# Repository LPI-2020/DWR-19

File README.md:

# Digital Waiter Robot (DWR -19)

Developed in:
- Projeto Integrador - LPI II (2021)

Members:
- Bruno Miguel Vasconcelos da Silva, a88289
- Diogo Miguel Cunha Fernandes, a88262
- Duarte Miguel Novo Rodrigues, a88259
- Francisco Lopes Salgado, a88231 
- João Pedro Dias Miranda, a88237
- José Tomás Lima de Abreu, a88218

Directed by:
- Luís André Magalhães de Barros

Short description (PT):
- A ideia do produto surgiu da necessidade de atuar perante o panorama pandémico (Covid-19), mais propriamente no auxílio a pessoas que se encontrem em isolamento.
- Uma pessoa em isolamento não pode ter contacto com o mundo exterior. Por este motivo, pensou-se em desenvolver um robô que faça chegar bens essenciais à pessoa em isolamento.
-	A função principal do produto será desempenhar o papel de um “empregado de mesa”, daí o nome “Waiter”. O termo “Digital” advém do facto de todas funcionalidades serem maioritariamente implementadas de forma digital, perfazendo o nome do robô “Digital Waiter Robot”.

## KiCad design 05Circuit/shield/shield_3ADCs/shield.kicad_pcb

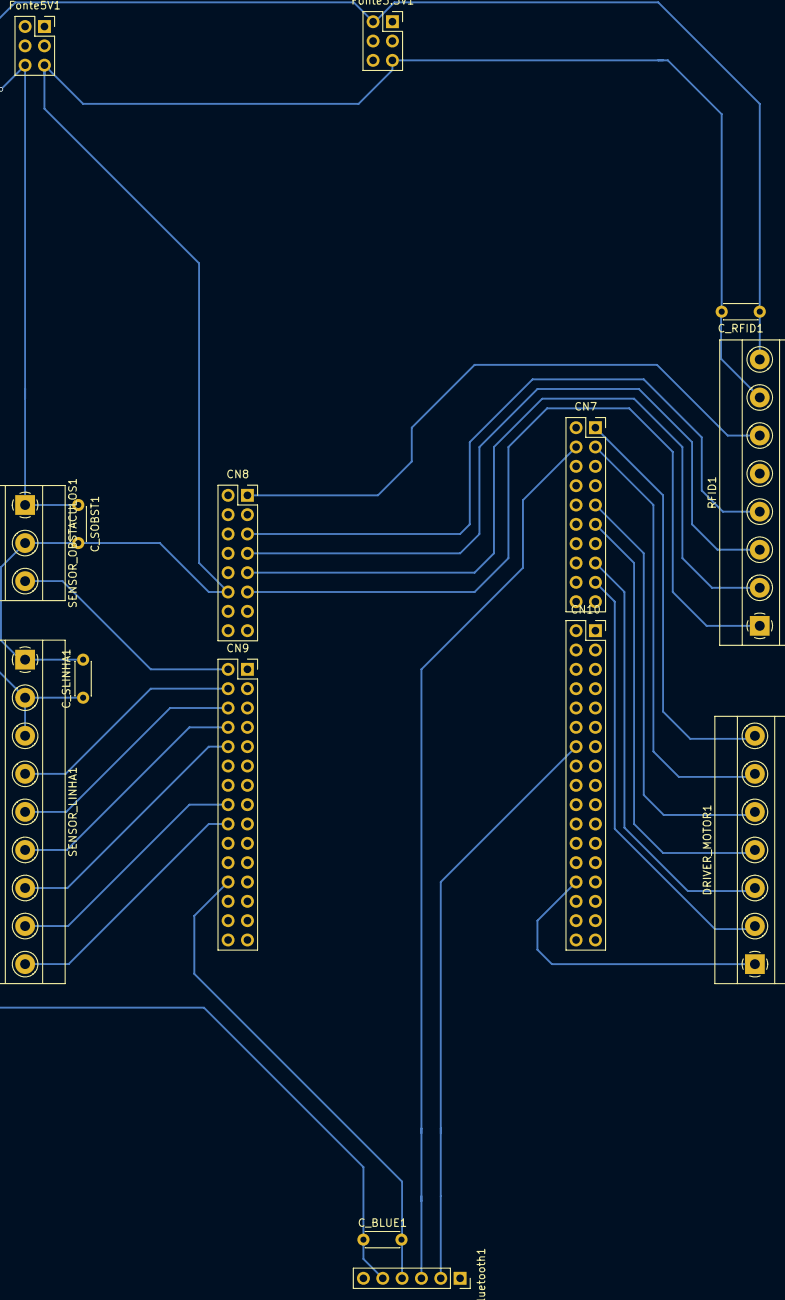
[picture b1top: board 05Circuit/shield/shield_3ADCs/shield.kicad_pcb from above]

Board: 2 copper layers, 15 parts (0 on the bottom side), 26 nets.

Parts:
CN7: Digital; PinSocket_2x10_P2.54mm_Vertical
CN8: Digital; PinSocket_2x08_P2.54mm_Vertical
CN9: Digital; PinSocket_2x15_P2.54mm_Vertical
CN10: Digital; PinSocket_2x17_P2.54mm_Vertical
C_BLUE1: C; C_Disc_D4.3mm_W1.9mm_P5.00mm
C_RFID1: C; C_Disc_D4.3mm_W1.9mm_P5.00mm
C_SLINHA1: C; C_Disc_D4.3mm_W1.9mm_P5.00mm
C_SOBST1: C; C_Disc_D4.3mm_W1.9mm_P5.00mm
DRIVER_MOTOR1: Screw_Terminal_01x07; TerminalBlock_Phoenix_MKDS-1,5-7_1x07_P5.00mm_Horizontal
Fonte3.3V1, Fonte5V1: Digital; PinSocket_2x03_P2.54mm_Vertical
RFID1: Screw_Terminal_01x06; TerminalBlock_Phoenix_MKDS-1,5-8_1x08_P5.00mm_Horizontal
SENSOR_LINHA1: Screw_Terminal_01x09; TerminalBlock_Phoenix_MKDS-1,5-9_1x09_P5.00mm_Horizontal
SENSOR_OBSTACULOS1: Screw_Terminal_01x03; TerminalBlock_Phoenix_MKDS-1,5-3_1x03_P5.00mm_Horizontal
bluetooth1: Digital; PinSocket_1x06_P2.54mm_Vertical

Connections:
+3.3V: C_RFID1.1, C_SLINHA1.1, Fonte3.3V1.2, Fonte3.3V1.6, RFID1.8, SENSOR_LINHA1.2, SENSOR_LINHA1.3
+5V: C_BLUE1.1, C_SOBST1.1, Fonte5V1.2, Fonte5V1.6, SENSOR_OBSTACULOS1.1, bluetooth1.5
/AVDD: CN7.5, CN10.2
/NC: CN8.2, CN9.14
/PA3: CN9.2, SENSOR_OBSTACULOS1.3
/PA5: CN7.9, DRIVER_MOTOR1.5
/PA6: CN7.11, DRIVER_MOTOR1.4
/PA7: CN7.13, CN9.16, SENSOR_LINHA1.8
/PB6: CN10.14, bluetooth1.2
/PB8: CN7.1, DRIVER_MOTOR1.7
/PB9: CN7.3, DRIVER_MOTOR1.6
/PB15: CN7.4, bluetooth1.3
/PC0: CN9.4, SENSOR_LINHA1.4
/PC3: CN9.6, SENSOR_LINHA1.5
/PC8: CN8.1, RFID1.6
/PC10: CN8.5, RFID1.4
/PC11: CN8.7, RFID1.3
/PC12: CN8.9, RFID1.2
/PD2: CN8.11, RFID1.1
/PD14: CN7.15, DRIVER_MOTOR1.3
/PD15: CN7.17, DRIVER_MOTOR1.2
/PE2: CN9.13, CN10.26
/PF2: CN9.18, SENSOR_LINHA1.9
/PF3: CN9.8, SENSOR_LINHA1.6
/PF5: CN9.10, SENSOR_LINHA1.7
GND: CN7.7, CN8.12, CN8.14, CN9.11, CN9.24, CN10.6, CN10.18, CN10.21, CN10.28, C_BLUE1.2, C_RFID1.2, C_SLINHA1.2, C_SOBST1.2, DRIVER_MOTOR1.1, Fonte3.3V1.1, Fonte3.3V1.5, Fonte5V1.1, Fonte5V1.5, RFID1.7, SENSOR_LINHA1.1, SENSOR_OBSTACULOS1.2, bluetooth1.4

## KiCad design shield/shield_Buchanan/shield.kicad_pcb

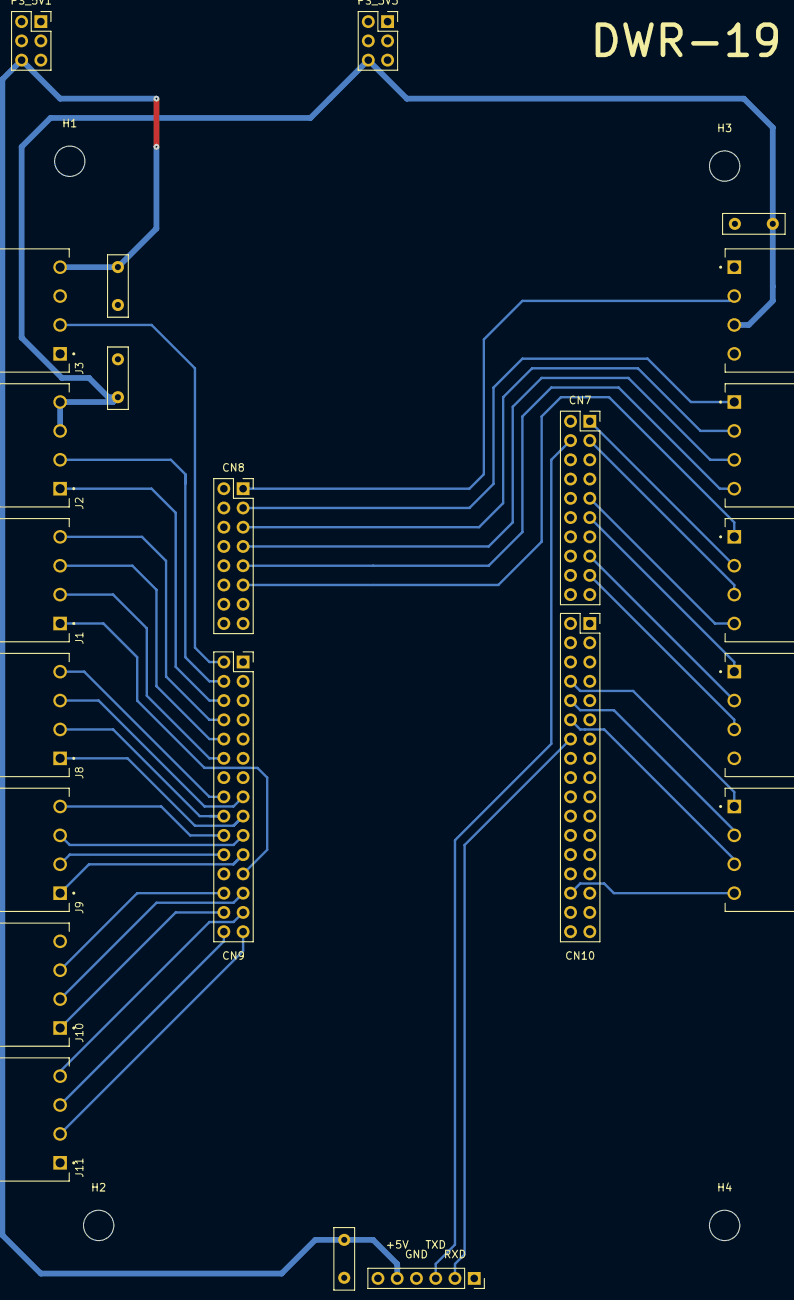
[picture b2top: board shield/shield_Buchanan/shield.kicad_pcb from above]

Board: 2 copper layers, 27 parts (0 on the bottom side), 45 nets.

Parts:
Bluetooth1: Conn_01x06; PinSocket_1x06_P2.54mm_Vertical
CN7: Conn_02x10_Odd_Even; PinSocket_2x10_P2.54mm_Vertical
CN8: Conn_02x08_Odd_Even; PinSocket_2x08_P2.54mm_Vertical
CN9: Conn_02x15_Odd_Even; PinSocket_2x15_P2.54mm_Vertical
CN10: Conn_02x17_Odd_Even; PinSocket_2x17_P2.54mm_Vertical
C_BLUE1: C; C_Disc_D8.0mm_W2.5mm_P5.00mm
C_RFID1: C; C_Disc_D8.0mm_W2.5mm_P5.00mm
C_SLINHA1: C; C_Disc_D8.0mm_W2.5mm_P5.00mm
C_SOBST1: C; C_Disc_D8.0mm_W2.5mm_P5.00mm
H1, H2, H3, H4: MountingHole; MountingHole_4mm
J1, J2, J3, J4, J5, J6, J7, J8, J9, J10, J11, J12: Screw_Terminal_01x04; TE_284513-4
PS_3V3, PS_5V1: Screw_Terminal_02x03; PinSocket_2x03_P2.54mm_Vertical

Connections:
+3V3: C_RFID1.1, C_SLINHA1.1, J2.3, J2.4, J7.3, PS_3V3.2, PS_3V3.6
+5V: Bluetooth1.5, C_BLUE1.1, C_SOBST1.1, J3.4, PS_5V1.2, PS_5V1.6
AVDD: CN7.5, CN10.2
GND: Bluetooth1.4, CN7.7, CN8.12, CN8.14, CN9.11, CN9.24, CN10.6, CN10.18, CN10.21, CN10.28, C_BLUE1.2, C_RFID1.2, C_SLINHA1.2, C_SOBST1.2, J3.1, J3.3, J4.4, J7.1, J7.4, J10.4, PS_3V3.1, PS_3V3.5, PS_5V1.1, PS_5V1.5
NC: CN8.2, CN9.14
PA0: CN10.30, J12.4
PA3: CN9.2, J3.2
PA5: CN7.9, J5.4
PA6: CN7.11, J4.1
PA7: CN7.13, CN9.16, J8.4
PB1: CN10.8, J12.1
PB6: Bluetooth1.2, CN10.14
PB8: CN7.1, J5.2
PB9: CN7.3, J5.3
PB15: Bluetooth1.3, CN7.4
PC0: CN9.4, J2.2
PC2: CN10.10, J12.2
PC3: CN9.6, J2.1
PC8: CN8.1, J7.2
PC9: CN8.3, J6.1
PC10: CN8.5, J6.2
PC11: CN8.7, J6.3
PC12: CN8.9, J6.4
PD0: CN9.26, J10.3
PD1: CN9.28, J10.1
PD2: CN8.11, J5.1
PD14: CN7.15, J4.2
PD15: CN7.17, J4.3
PE2: CN9.13, CN10.26
PE3: CN9.21, J9.1
PE4: CN9.15, J8.3
PE5: CN9.17, J8.1
PE6: CN9.19, J9.3
PF0: CN9.22, J9.2
PF1: CN9.20, J9.4
PF2: CN9.18, J8.2
PF3: CN9.8, J1.4
PF4: CN10.12, J12.3
PF5: CN9.10, J1.3
PF7: CN9.25, J10.2
PF8: CN9.23, J1.1
PF9: CN9.27, J11.4
PF10: CN9.12, J1.2
PG0: CN9.30, J11.3
PG1: CN9.29, J11.2

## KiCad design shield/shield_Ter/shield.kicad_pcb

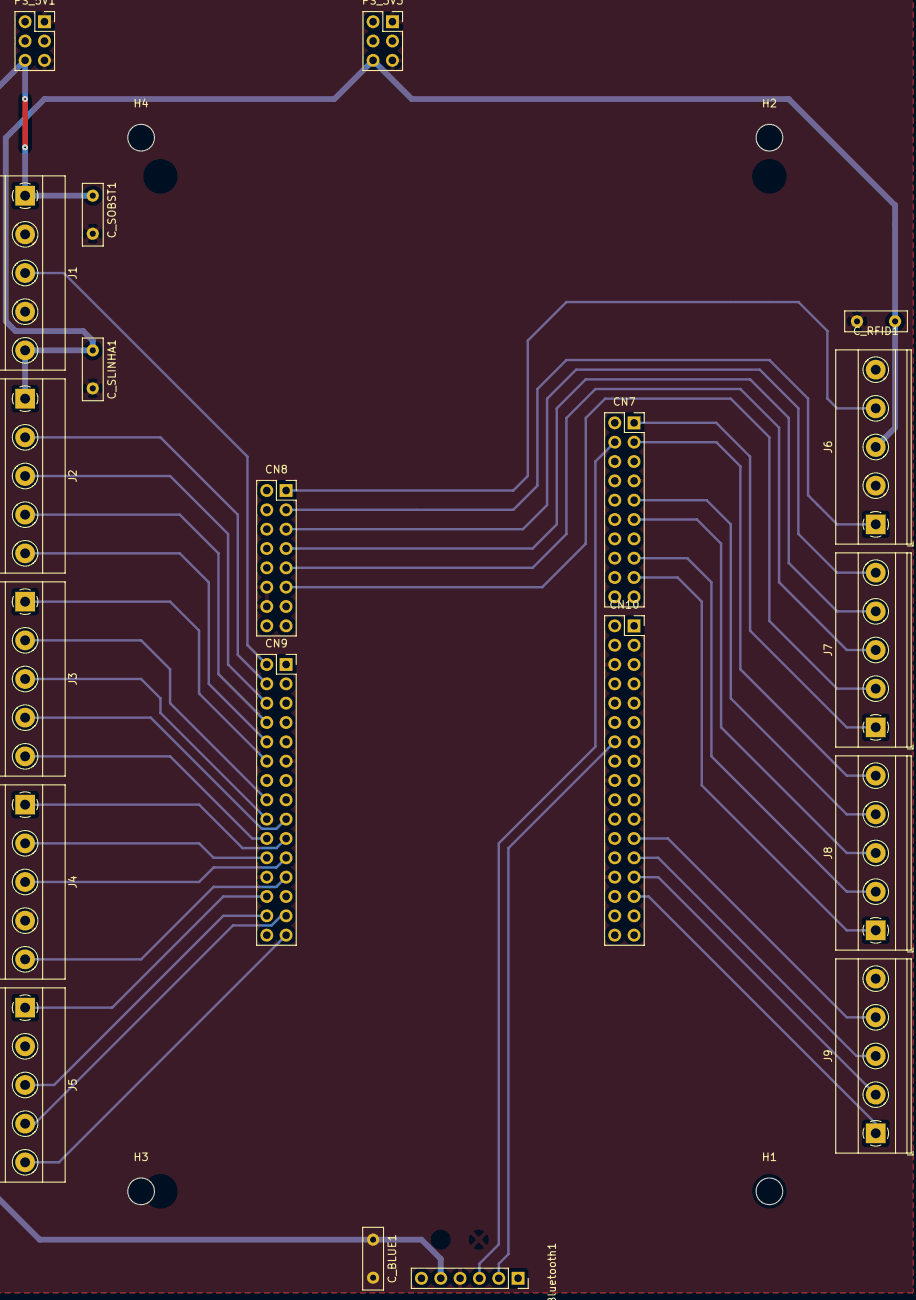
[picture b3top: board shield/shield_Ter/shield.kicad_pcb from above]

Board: 2 copper layers, 24 parts (0 on the bottom side), 42 nets.

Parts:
Bluetooth1: Conn_01x06; PinSocket_1x06_P2.54mm_Vertical
CN7: Conn_02x10_Odd_Even; PinSocket_2x10_P2.54mm_Vertical
CN8: Conn_02x08_Odd_Even; PinSocket_2x08_P2.54mm_Vertical
CN9: Conn_02x15_Odd_Even; PinSocket_2x15_P2.54mm_Vertical
CN10: Conn_02x17_Odd_Even; PinSocket_2x17_P2.54mm_Vertical
C_BLUE1: C; C_Disc_D8.0mm_W2.5mm_P5.00mm
C_RFID1: C; C_Disc_D8.0mm_W2.5mm_P5.00mm
C_SLINHA1: C; C_Disc_D8.0mm_W2.5mm_P5.00mm
C_SOBST1: C; C_Disc_D8.0mm_W2.5mm_P5.00mm
H1, H2, H3, H4: MountingHole; MountingHole_3.5mm
J1, J2, J3, J4, J5: Screw_Terminal_01x05; TerminalBlock_Phoenix_MKDS-1,5-5-5.08_1x05_P5.08mm_Horizont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
J6, J7, J8, J9: Screw_Terminal_01x04; TerminalBlock_Phoenix_MKDS-1,5-5-5.08_1x05_P5.08mm_Horizont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
PS_3V3, PS_5V1: Screw_Terminal_02x03; PinSocket_2x03_P2.54mm_Vertical

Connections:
+3V3: C_RFID1.1, C_SLINHA1.1, J1.5, J2.1, J6.3, PS_3V3.2, PS_3V3.6
+5V: Bluetooth1.5, C_BLUE1.1, C_SOBST1.1, J1.1, PS_5V1.2, PS_5V1.6
AVDD: CN7.5, CN10.2
GND: Bluetooth1.4, CN7.7, CN8.12, CN8.14, CN9.11, CN9.24, CN10.6, CN10.18, CN10.21, CN10.28, C_BLUE1.2, C_RFID1.2, C_SLINHA1.2, C_SOBST1.2, J1.2, J1.4, J4.4, J6.2, J6.5, J9.5, PS_3V3.1, PS_3V3.5, PS_5V1.1, PS_5V1.5
NC: CN8.2, CN9.14
PA3: CN9.2, J1.3
PA5: CN7.9, J8.4
PA6: CN7.11, J8.3
PA7: CN7.13, CN9.16, J3.2
PB6: Bluetooth1.2, CN10.14
PB8: CN7.1, J7.1
PB9: CN7.3, J8.5
PB15: Bluetooth1.3, CN7.4
PC0: CN9.4, J2.2
PC3: CN9.6, J2.3
PC8: CN8.1, J6.4
PC9: CN8.3, J6.1
PC10: CN8.5, J7.5
PC11: CN8.7, J7.4
PC12: CN8.9, J7.3
PD0: CN9.26, J5.1
PD1: CN9.28, J5.3
PD2: CN8.11, J7.2
PD14: CN7.15, J8.2
PD15: CN7.17, J8.1
PE2: CN9.13, CN10.26
PE3: CN9.21, J4.3
PE5: CN9.17, J3.4
PE6: CN9.19, J4.1
PE10: CN10.23, J9.4
PE12: CN10.25, J9.3
PE14: CN10.27, J9.2
PE15: CN10.29, J9.1
PF0: CN9.22, J4.2
PF1: CN9.20, J3.5
PF2: CN9.18, J3.3
PF3: CN9.8, J2.4
PF5: CN9.10, J2.5
PF8: CN9.23, J4.5
PF9: CN9.27, J5.4
PF10: CN9.12, J3.1
PG1: CN9.29, J5.5

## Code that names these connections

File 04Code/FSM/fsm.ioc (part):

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Mcu.UserName=STM32F767ZITx
PC10.Signal=SPI3_SCK
PC12.Signal=SPI3_MOSI
PB14.GPIO_Label=DEBUG_LRED
PC0.GPIOParameters=GPIO_Label
PC0.GPIO_Label=SENSOR1
PA3.GPIOParameters=GPIO_Label
PB0.GPIO_Label=DEBUG_LGREEN
PA6.GPIO_Label=IN1_LEFT
PB6.GPIO_Label=BLUET_TX
PD2.GPIOParameters=GPIO_Label
PB15.Signal=USART1_RX
PD9.Mode=Asynchronous
RCC.SYSCLKSource=RCC_SYSCLKSOURCE_PLLCLK
PD15.GPIOParameters=GPIO_Label
PB6.Signal=USART1_TX
PB6.Mode=Asynchronous
PC3.Signal=ADCx_IN13
PD8.Signal=USART3_TX
PF10.GPIO_Label=SENSOR6
RCC.HSE_VALUE=25000000
PB0.GPIOParameters=GPIO_Label
PB1.GPIO_Label=BUZZER
PB7.Signal=GPIO_Output
PF8.Mode=IN6
PF3.Signal=ADC3_IN9
PB6.GPIOParameters=GPIO_Label
PB7.GPIO_Label=DEBUG_LBLUE
PC8.GPIOParameters=GPIO_PuPd,GPIO_Label
Mcu.Package=LQFP144
PB9.Signal=GPIO_Output
PB1.Signal=GPIO_Output
PA6.Signal=GPIO_Output
PF8.GPIOParameters=GPIO_Label
PF5.GPIO_Label=SENSOR5
PF8.Signal=ADC3_IN6
PA5.GPIOParameters=GPIO_Label
PC11.Mode=Full_Duplex_Master
PB14.GPIOParameters=GPIO_Label
PF5.Signal=ADC3_IN15
PF10.Mode=IN8
PF3.GPIO_Label=SENSOR4
PD15.Signal=S_TIM4_CH4
PA3.Signal=ADCx_IN3
PA6.GPIOParameters=GPIO_Label
PD15.GPIO_Label=PWM_LEFT
PB8.GPIOParameters=GPIO_Label
PF3.Mode=IN9
PB9.GPIO_Label=IN1_RIGHT
PC11.Signal=SPI3_MISO
PC8.Signal=GPIO_Input
PC10.Mode=Full_Duplex_Master
PD9.Signal=USART3_RX
PC0.Signal=ADCx_IN10
PF5.Mode=IN15
PF8.GPIO_Label=SENSOR8
PB9.GPIOParameters=GPIO_Label
PC3.GPIOParameters=GPIO_Label
PC8.GPIO_Label=USER_BTN
PB8.GPIO_Label=PWM_RIGHT
PB7.GPIOParameters=GPIO_Label
PF5.GPIOParameters=GPIO_Label
PD8.Mode=Asynchronous
PF3.GPIOParameters=GPIO_Label
PB14.Signal=GPIO_Output
PA5.Signal=GPIO_Output
PC12.Mode=Full_Duplex_Master
board=custom
PB15.Mode=Asynchronous
PB15.GPIO_Label=BLUET_RX
PF10.Signal=ADC3_IN8
PD14.GPIO_Label=IN2_LEFT
PB15.GPIOParameters=GPIO_Label
Mcu.Name=STM32F767ZITx
PD14.Signal=GPIO_Output
PC8.GPIO_PuPd=GPIO_PULLDOWN
PD14.GPIOParameters=GPIO_Label
RCC.SYSCLKFreq_VALUE=216000000
PA5.GPIO_Label=IN2_RIGHT
PF10.GPIOParameters=GPIO_Label
PB8.Signal=S_TIM4_CH3
PC3.GPIO_Label=SENSOR3
PD2.Signal=GPIO_Output
PB0.Signal=GPIO_Output
PD2.GPIO_Label=SPI3_SDA
PA3.GPIO_Label=OBS_DETECTOR
PB1.GPIOParameters=GPIO_Label

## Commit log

2021-02-26 add etapa 0
2021-02-26 To use in the future
2021-03-08 Etapa1-v1
2021-03-08 Added working time table
2021-03-08 Logbook
2021-03-10 planeamento acabado
2021-03-11 Added components
2021-03-15 Starting Etapa1
2021-03-17 Etapa1
2021-03-18 fast update
2021-03-18 Etapa1 done
2021-03-25 Minor corrections
2021-03-25 table index
2021-03-25 etapa 1 done v2
2021-03-25 Etapa1 pdf
2021-03-25 References fix
2021-03-29 Logbook update
2021-03-31 read sensor values with DMA
2021-03-31 Added stop mark sensor Flowchart
2021-03-31 Added obstacles sensor flowchart
2021-04-01 Added System diagrams
2021-04-01 Sensors readme update
2021-04-01 Module readme update
2021-04-01 Joao/Duarte update logbook -> day 31/03
2021-04-14 Added RFID code, Updated logbook and components list
2021-04-14 Updated RFID Readme files
2021-05-03 System diagram update
2021-05-04 Logbook yesterday
2021-05-04 pdf Titles changed
2021-05-05 Added documentation
2021-05-05 Detectors debug
2021-05-05 add seguidor de linha
2021-05-05 update RFID module
2021-06-01 Working on Stop Sensors
2021-06-01 linefollower code
2021-06-02 qtr dma
2021-06-03 Controlador PID feito (valores Kp,Ki,Kd escolhidos) | diagrama PID
2021-06-03 Stop sensors done
2021-06-03 turn
2021-06-04 Added battery schema
2021-06-04 Added Bluetooth
2021-06-04 rotate clean code
2021-06-05 Adding comments
2021-06-05 little changes on PID algorithm
2021-06-06 update log book
2021-06-07 Line follower
2021-06-07 Working on PID
2021-06-07 Speed extra
2021-06-07 Get speed macro
2021-06-07 RFID - SPI3 (needs testing)
    Code for RFID to work with SPI3.
    - Changed SP1 to SPI3: PINS A6, A7, A8 changed to C10, C11 and P12
2021-06-07 Updated Logbook and added Perifericos
2021-06-07 Testing move module
2021-06-07 Bluetooth - Added USART 1 functionality
2021-06-08 some corrections line top speed. Not working anyway
2021-06-08 Revert "Updated Logbook and added Perifericos"
    This reverts commit dbdd964fc060a66478d0325b46005da320524534.
2021-06-08 Updated Bluetooth, Added Cmd parsing
2021-06-08 pin excel v1
2021-06-08 perifericos updat
    e
2021-06-08 Merging FSM configs
2021-06-08 edit pinout excel, add pinout kicad
2021-06-09 line sensor 6 adc
2021-06-09 Testing stop sensors
2021-06-09 errors detected: lacks 'lf_rotate' from lineFollower
2021-06-09 shield 7 ADCs e perifericos
2021-06-09 added debounce
2021-06-09 Working on lfollower
2021-06-09 Cleaned RFID.c (only SPI3 folder)
    Won't modify SPI1 RFID to in order to keep a backup
2021-06-09 Added Comments
2021-06-09 Added Diagramas
2021-06-09 merging files to FSM
2021-06-10 Changed pins and peripherals in use FSM
2021-06-10 pcb conetores demasiado caros
2021-06-10 word
2021-06-10 PCB with Aquario con
2021-06-10 Corrected PCB
2021-06-10 PCB ready with buchanan conectors
2021-06-10 Obstacle detector
2021-06-10 QTR version
2021-06-10 texto maquina de estados
2021-06-10 Perifericos
2021-06-10 Diogo Updates
2021-06-10 Update PCB with new pins -> ADC3
2021-06-10 pcb adc 3
2021-06-10 PID text uptade
2021-06-10 read_RFID function and struct | test rfid in tests.c
2021-06-10 Update PID and State Machine text
2021-06-10 Test stop sensors
2021-06-11 rfid checks
2021-06-11 FSM testing
2021-06-11 Updated Diagrams
2021-06-11 Corrected RFID SPI3
2021-06-11 Test peripherals
2021-06-11 last update Kicad
2021-06-11 word pid
2021-06-12 add PID_ISR
2021-06-12 Update Bluetooth
2021-06-12 pid word update
2021-06-12 motion module
2021-06-12 motion
2021-06-12 receives one time and dont receives more chars
2021-06-12 PID followchart upadate. Word update
2021-06-12 Review word FSMPID
2021-06-12 rm ~docx
2021-06-12 Removing commented code
2021-06-12 qtr get digital/analog values
2021-06-12 Timeout module
2021-06-12 Rellocated timers. Timeout timer max 140sec
2021-06-12 Timeout update
2021-06-13 writing tests
2021-06-13 logbook components
2021-06-13 Error module
2021-06-13 Buracos 4mm
2021-06-13 motion testing
2021-06-13 timeout period
2021-06-13 Ficheiros Gerber!
2021-06-13 Testing Cross Detector
2021-06-13 testing rfid
2021-06-14 Added deobunce
2021-06-14 Capitulo Alimentacao e Mecanico
2021-06-14 Add ordem trabalhos
2021-06-14 testing
2021-06-14 receiving in fsm
2021-06-14 atulizaçao do logbook | lista de componentes | ordem de trabalhos
2021-06-14 fotos dos materiais
2021-06-14 fsm bluet using
2021-06-14 DMA (pouca coisa)
2021-06-14 dia pouco produtivo
2021-06-14 merging
2021-06-14 pid completed - no review done
2021-06-15 PID Word update (Offset explained)-> no review
2021-06-15 DMA acabado
2021-06-15 stop condition in motion isr
2021-06-15 Testing debounce
2021-06-15 circuitos de alimentacao update
2021-06-15 Diagrams Updated
2021-06-15 circuito mecanico - 1 review
2021-06-15 lineflw ok
2021-06-15 testing fsm
2021-06-15 correcao PID adc diagrama
2021-06-15 DMA -> EN
2021-06-15 Tsting Fsm
2021-06-16 relatorio - timers
2021-06-16 Uart added and small fixes to spi
2021-06-16 Updated Diagrams (~98% done)
2021-06-16 next move
2021-06-16 Diagrams 99% done - pdf preview available
    Still needs front sensor
2021-06-16 comentarios e possiveis correcoes SPI
2021-06-16 rfid
2021-06-16 UART possiveis correcoes
2021-06-16 atualização do SPI | inicio da tabela de perifericos
2021-06-16 mudança da pasta da shield
2021-06-16 Completed Mechanical Diagrams
2021-06-16 Fixing timeouts
2021-06-17 introducao
2021-06-17 update relatorio RFID e Bluetooth
2021-06-17 Added Bluetooth drawio diagram (not completed)
2021-06-17 Topicos Relatorio
2021-06-17 Tabelas de perifericos
2021-06-17 atualizaçao dos capitulos
2021-06-17 corpo do relatorio
2021-06-17 rfid number: cross duarte's bedroom
2021-06-17 fsm returning
2021-06-17 FSM finished
2021-06-18 Added sensores
2021-06-18 sys_diagram_v2
2021-06-18 Bluetooth Diagram
2021-06-18 DMA e ADC corrigido e adicionado ao relatorio
2021-06-18 Arquitetura e Modulos Utilizados in progress
2021-06-18 Updated diagrams (3D Model)
2021-06-18 Corrected UART and merged it with Perifericos
    Still needs tables
2021-06-18 Corrected and Merged SPI to Perifericos
    Still needs configuration table
2021-06-18 Diagrama PID corrigido
2021-06-18 FSM explanation done
2021-06-18 peripheral update
2021-06-18 Changed Configurations, Added Bluetooth and RFID modules datasheets
2021-06-18 Review fsm pid
2021-06-18 mais uma correcao diagrama PID
2021-06-18 Review pid
2021-06-18 UART and SPI
2021-06-18 Implementacao em sw
2021-06-18 Caps relatorio update
2021-06-18 SW modules
2021-06-18 retirar ficheiros temporarios WORD
2021-06-18 Fluxograma PID corrigido
2021-06-18 Diagrama PID alteradoQ
2021-06-18 Controller
2021-06-18 Cleaning code
2021-06-19 PID + CAlimentacao + PCB(Shield)
2021-06-19 Upadated 3D model
    Added RFID support and side button. Missing switch, charging port and obstacle sensor.
2021-06-19 continuing implementacao_soft
2021-06-19 New module cmdparser
2021-06-19 veiculos autonomos
2021-06-19 conclusoes
2021-06-19 Rm ~word file
2021-06-19 Check route
2021-06-19 turning 180 degrees in the origin
2021-06-19 move left alteration
2021-06-19 Conclusoes e trabalho futuro
2021-06-19 parte mecanica e de software adicionada ao Relatorio
2021-06-19 correcoes
2021-06-19 diagrama de Gantt e relatorio (falta rever)
2021-06-20 alteracoes ao DMA ADC e timers
2021-06-20 Correcoes relatorio
2021-06-20 Correcoes2
2021-06-20 correcoes_tomas completed
2021-06-20 mapeamento de memoria
2021-06-20 RE do PID e motores
2021-06-20 Testews obstaculs
2021-06-20 review G1_DWR-19
2021-06-20 Resultados ecxp
2021-06-20 Final1
2021-06-20 Relatorio
2021-06-20 Alteracoes Chico e Bruno
2021-06-20 Alteracoes relatorio DMA
2021-06-20 Alteracoes paginacao
2021-06-20 Referencias feitas
2021-06-20 Rotate at origin done
2021-06-20 Remote Start DWR
2021-06-21 Added route2
2021-06-21 Removed unnecessary files
2021-06-21 Added datasheets
2021-06-21 Added new app menu
2021-06-21 Added github link
2021-06-21 Finished 3D model
2021-06-21 Relatorio LB
2021-06-21 Sys diagram update
2021-06-21 graficos das açoes do PID2
2021-06-21 conclusao
2021-06-21 pid testing
2021-06-21 correct pid values in relatorio
2021-06-22 last updates relatorio
2021-06-22 Added LeSpeciale
    Nem acredito que gastei 4 horas nisto. Não acrescentei o pdf para não dar arruinar a surpresa.
2021-06-22 relatorio sem videos
2021-06-22 Add links relatorio
2021-06-22 Remote control!
2021-06-22 added cr
2021-06-22 Update LeSpeciale
    Y tho?
2021-06-22 src code
2021-06-22 last
2021-06-22 Job Done
2021-06-22 apresentacao
2021-06-22 Presentation
2021-06-23 Added Final Presentation
